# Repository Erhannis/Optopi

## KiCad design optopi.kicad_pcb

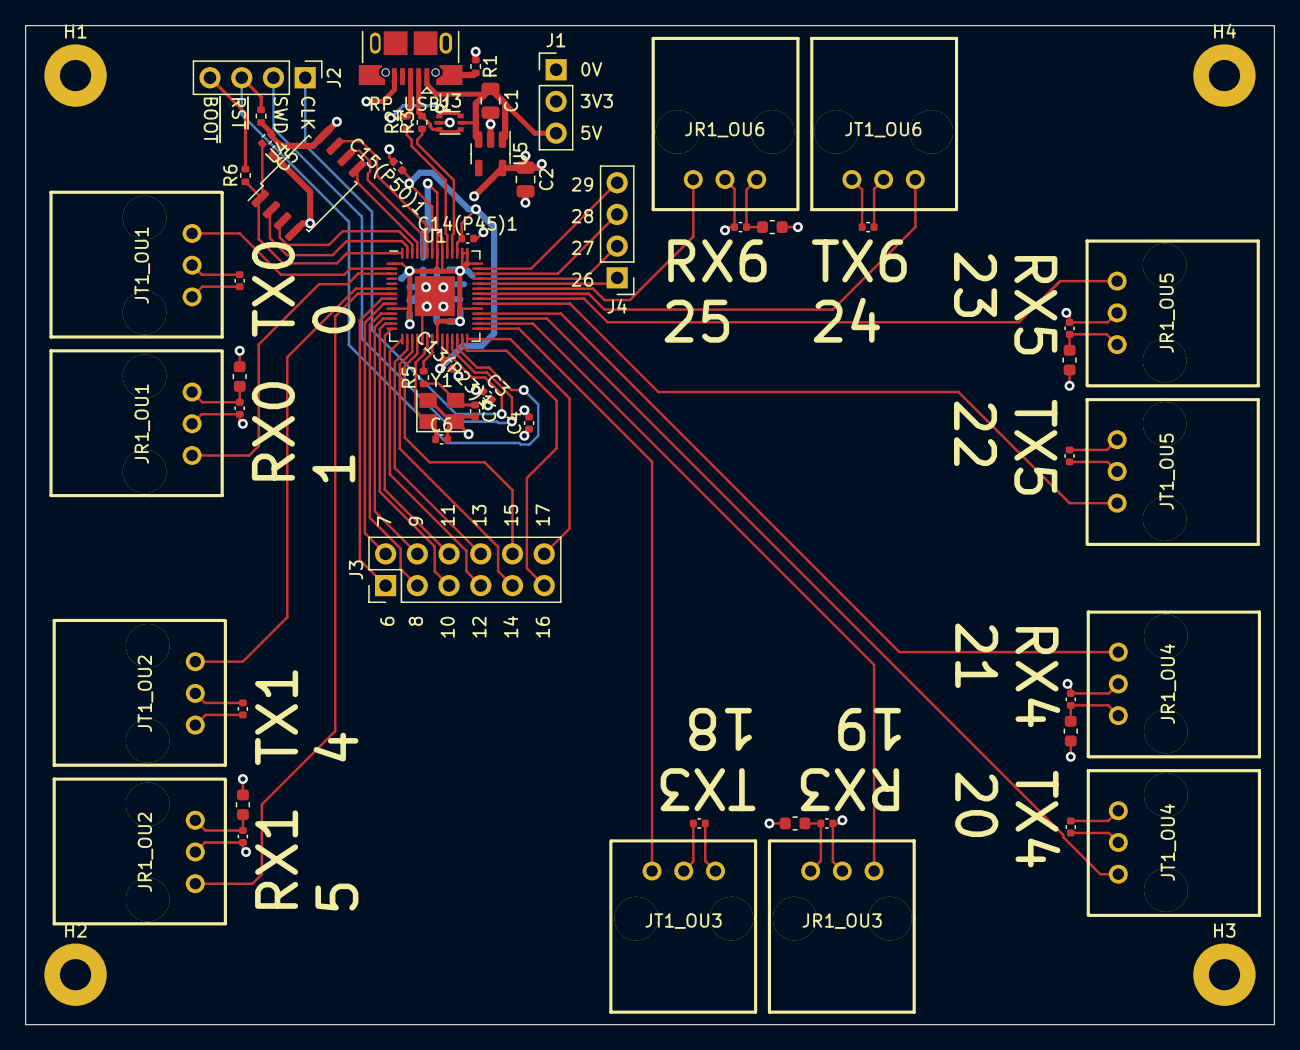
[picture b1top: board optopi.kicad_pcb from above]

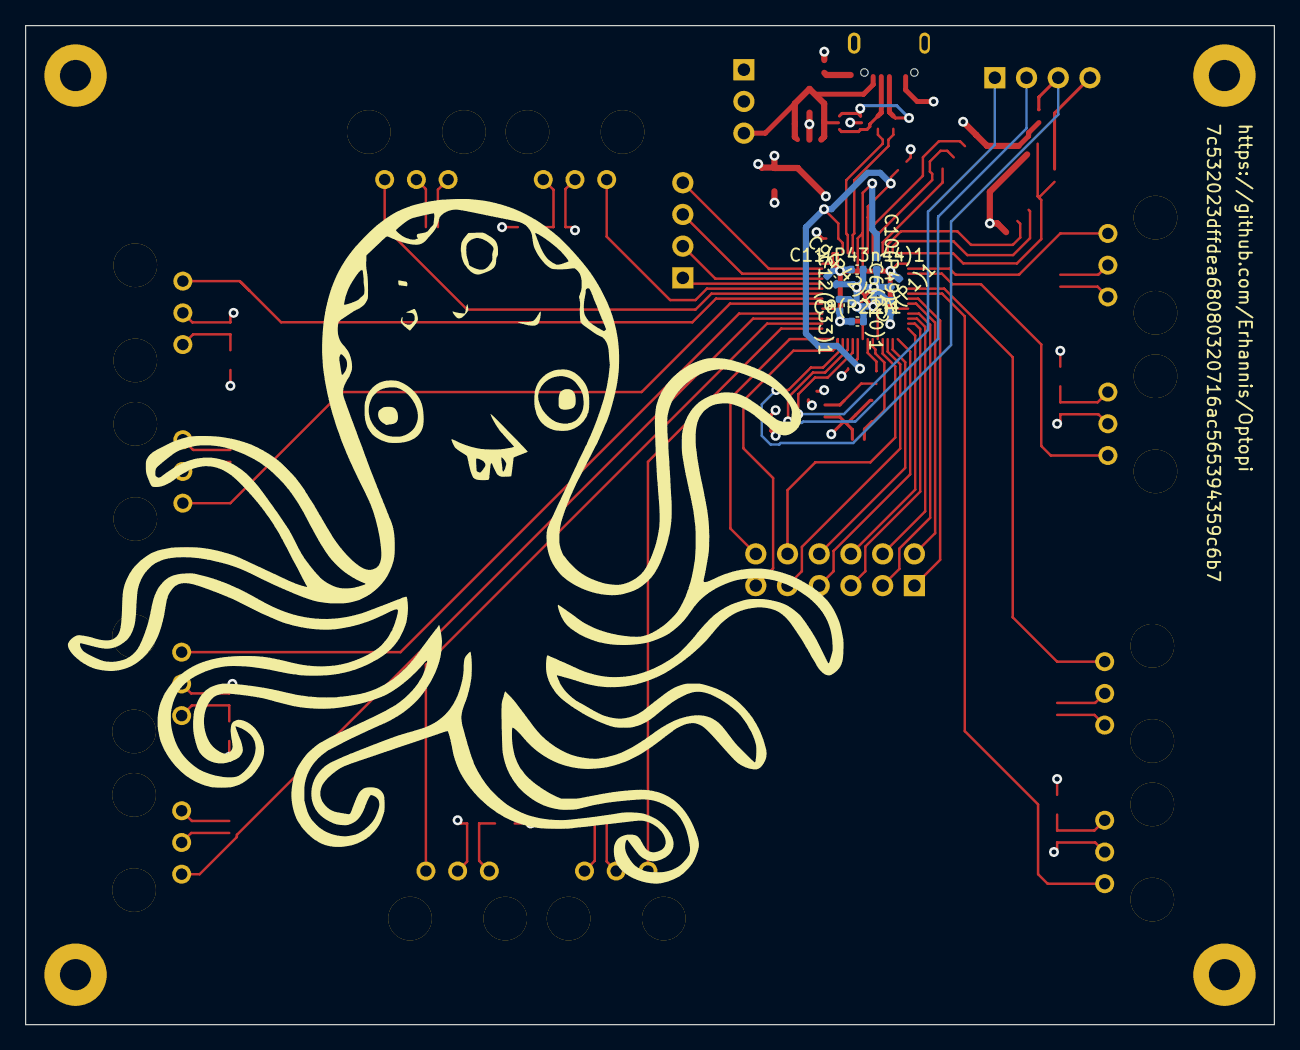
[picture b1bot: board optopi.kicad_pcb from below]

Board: 4 copper layers, 100.0 x 80.0 mm, 68 parts (7 on the bottom side), 56 nets.

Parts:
C1, C2: 10uF; C_0805_2012Metric
C1_OU1, C1_OU2, C1_OU3, C1_OU4, C1_OU5, C1_OU6, C2_OU1, C2_OU2, C2_OU3, C2_OU4, C2_OU5, C2_OU6, C3, C4, C5, C6(P10)1, C7(P1)1, C8(P22)1, C9(P42)1, C10(P49)1, C12(P33)1, C13(P23)1, C15(P50)1: 100nF; C_0402_1005Metric
C6, C7: 35pF; C_0402_1005Metric
C11(P43n44)1, C14(P45)1: 1uF; C_0402_1005Metric
H1, H2, H3, H4: MountingHole_Pad; MountingHole_2.5mm_Pad
J1: Conn_01x03_Pin; PinHeader_1x03_P2.54mm_Vertical
J2, J4: Conn_01x04_Pin; PinHeader_1x04_P2.54mm_Vertical
J3: Conn_02x06_Odd_Even; PinHeader_2x06_P2.54mm_Vertical
JR1_OU1, JR1_OU2, JR1_OU3, JR1_OU4, JR1_OU5, JR1_OU6: ZGY135/T9(PLR); OPTO-TH_ZGY135-T9-PLR
JT1_OU1, JT1_OU2, JT1_OU3, JT1_OU4, JT1_OU5, JT1_OU6: ZGY133/T9(PLT); OPTO-TH_ZGY135-T9-PLR
L1_OU1, L1_OU2, L1_OU3, L1_OU4, L1_OU5, L1_OU6: 47uH; L_0603_1608Metric
R1: 1M; R_0402_1005Metric
R2, R3: 27; R_0402_1005Metric
R4, R7: 10K; R_0402_1005Metric
R5: 1K; R_0402_1005Metric
R6: 1k; R_0402_1005Metric
RP_USB1: USB_B_Micro; USB_Micro-B_XKB_U254-051T-4BH83-F1S
U1: RP2040; QFN-56-1EP_7x7mm_P0.4mm_EP3.2x3.2mm
U3: USBLC6-2P6; SOT-666
U4: W25Q128JVS; SOIC-8_5.23x5.23mm_P1.27mm
U5: AP2112K-3.3; SOT-23-5
Y1: 12MHz; Crystal_SMD_3225-4Pin_3.2x2.5mm

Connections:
+1V2: C13(P23)1.1, C14(P45)1.1, C15(P50)1.1, U1.23 (DVDD), U1.45 (VREG_VOUT), U1.50 (DVDD)
+3V3: C2.1, C2_OU1.2, C2_OU2.2, C2_OU3.2, C2_OU4.2, C2_OU5.2, C2_OU6.2, C3.1, C4.1, C5.1, C6(P10)1.1, C7(P1)1.1, C8(P22)1.1, C9(P42)1.1, C10(P49)1.1, C11(P43n44)1.1, C12(P33)1.1, J1.2, JT1_OU1.2 (VCC), JT1_OU2.2 (VCC), JT1_OU3.2 (VCC), JT1_OU4.2 (VCC), JT1_OU5.2 (VCC), JT1_OU6.2 (VCC), L1_OU1.1, L1_OU2.1, L1_OU3.1, L1_OU4.1, L1_OU5.1, L1_OU6.1, R4.1, R7.2, U1.1 (IOVDD), U1.10 (IOVDD), U1.22 (IOVDD), U1.33 (IOVDD), U1.42 (IOVDD), U1.43 (ADC_AVDD), U1.44 (VREG_IN), U1.48 (USB_VDD), U1.49 (IOVDD), U4.8 (VCC), U5.5 (VOUT)
+5V: C1.1, J1.3, RP_USB1.1 (VBUS), U3.5 (VBUS), U5.1 (VIN), U5.3 (EN)
/QSPI_CS: R6.1, R7.1, U1.56 (QSPI_SS), U4.1 (~CS)
/QSPI_DATA[0]: U1.53 (QSPI_SD0), U4.5 (DI(IO0))
/QSPI_DATA[1]: U1.55 (QSPI_SD1), U4.2 (DO(IO1))
/QSPI_DATA[2]: U1.54 (QSPI_SD2), U4.3 (IO2)
/QSPI_DATA[3]: U1.51 (QSPI_SD3), U4.7 (IO3)
/QSPI_SCK: U1.52 (QSPI_SCLK), U4.6 (CLK)
/RP_SWCLK: J2.1, U1.24 (SWCLK)
/RP_SWD: J2.2, U1.25 (SWD)
/RP_UD+: R2.1, U1.47 (USB_DP)
/RP_UD-: R3.1, U1.46 (USB_DM)
/USB_BOOT: J2.4, R6.2
/optic_uart1/RX: JR1_OU1.1 (VOUT), U1.3 (GPIO1)
/optic_uart1/TX: JT1_OU1.3 (VIN), U1.2 (GPIO0)
/optic_uart2/RX: JR1_OU2.1 (VOUT), U1.7 (GPIO5)
/optic_uart2/TX: JT1_OU2.3 (VIN), U1.6 (GPIO4)
/optic_uart3/RX: JR1_OU3.1 (VOUT), U1.30 (GPIO19)
/optic_uart3/TX: JT1_OU3.3 (VIN), U1.29 (GPIO18)
/optic_uart4/RX: JR1_OU4.1 (VOUT), U1.32 (GPIO21)
/optic_uart4/TX: JT1_OU4.3 (VIN), U1.31 (GPIO20)
/optic_uart5/RX: JR1_OU5.1 (VOUT), U1.35 (GPIO23)
/optic_uart5/TX: JT1_OU5.3 (VIN), U1.34 (GPIO22)
/optic_uart6/RX: JR1_OU6.1 (VOUT), U1.37 (GPIO25)
/optic_uart6/TX: JT1_OU6.3 (VIN), U1.36 (GPIO24)
/~RESET: J2.3, R4.2, U1.26 (RUN)
GND: C1.2, C1_OU1.2, C1_OU2.2, C1_OU3.2, C1_OU4.2, C1_OU5.2, C1_OU6.2, C2.2, C2_OU1.1, C2_OU2.1, C2_OU3.1, C2_OU4.1, C2_OU5.1, C2_OU6.1, C3.2, C4.2, C5.2, C6.2, C6(P10)1.2, C7.2, C7(P1)1.2, C8(P22)1.2, C9(P42)1.2, C10(P49)1.2, C11(P43n44)1.2, C12(P33)1.2, C13(P23)1.2, C14(P45)1.2, C15(P50)1.2, H1.1, H2.1, H3.1, H4.1, J1.1, JR1_OU1.2 (GND), JR1_OU2.2 (GND), JR1_OU3.2 (GND), JR1_OU4.2 (GND), JR1_OU5.2 (GND), JR1_OU6.2 (GND), JT1_OU1.1 (GND), JT1_OU2.1 (GND), JT1_OU3.1 (GND), JT1_OU4.1 (GND), JT1_OU5.1 (GND), JT1_OU6.1 (GND), R1.1, RP_USB1.5 (GND), U1.19 (TESTEN), U1.57 (GND), U3.2 (GND), U4.4 (GND), U5.2 (GND), Y1.2, Y1.4
unnamed: C7.1, R5.1, Y1.3
unnamed: J3.1, U1.8 (GPIO6)
unnamed: J3.2, U1.9 (GPIO7)
unnamed: J3.3, U1.11 (GPIO8)
unnamed: J3.4, U1.12 (GPIO9)
unnamed: J3.5, U1.13 (GPIO10)
unnamed: J3.6, U1.14 (GPIO11)
unnamed: J3.7, U1.15 (GPIO12)
unnamed: J3.8, U1.16 (GPIO13)
unnamed: J3.9, U1.17 (GPIO14)
unnamed: J3.10, U1.18 (GPIO15)
unnamed: J3.11, U1.27 (GPIO16)
unnamed: J3.12, U1.28 (GPIO17)
unnamed: J4.1, U1.38 (GPIO26_ADC0)
unnamed: J4.2, U1.39 (GPIO27_ADC1)
unnamed: J4.3, U1.40 (GPIO28_ADC2)
unnamed: J4.4, U1.41 (GPIO29_ADC3)
unnamed: C1_OU1.1, JR1_OU1.3 (VCC), L1_OU1.2
unnamed: C1_OU2.1, JR1_OU2.3 (VCC), L1_OU2.2
unnamed: C1_OU3.1, JR1_OU3.3 (VCC), L1_OU3.2
unnamed: C1_OU4.1, JR1_OU4.3 (VCC), L1_OU4.2
unnamed: C1_OU5.1, JR1_OU5.3 (VCC), L1_OU5.2
unnamed: C1_OU6.1, JR1_OU6.3 (VCC), L1_OU6.2
unnamed: R2.2, RP_USB1.3 (D+), U3.1 (I/O1), U3.6 (I/O1)
unnamed: R3.2, RP_USB1.2 (D-), U3.3 (I/O2), U3.4 (I/O2)
unnamed: R1.2, RP_USB1.6 (Shield)
unnamed: C6.1, U1.20 (XIN), Y1.1
unnamed: R5.2, U1.21 (XOUT)

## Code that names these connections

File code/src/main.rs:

#![no_std]
#![no_main]

mod pio_run;
mod opto_uart;

use embedded_hal::digital::OutputPin;
use opto_uart::toggle_uart_tx_pin;
use pio_run::uart_tx_putc;
use rp_pico::{entry, pac::clocks};
use defmt::*;
use defmt_rtt as _;
use panic_probe as _;
use core::{fmt::Write, str};

use rp2040_hal::{self as bsp, gpio::{DynBankId, DynPinId}};

use bsp::{
    clocks::{init_clocks_and_plls, Clock},
    pac,
    sio::Sio,
    watchdog::Watchdog,
};

use rp2040_hal::{gpio::Pins, uart::{DataBits, StopBits, UartConfig, UartPeripheral}};
use rp2040_hal::fugit::RateExtU32;

const XOSC_CRYSTAL_FREQ: u32 = 12_000_000; // Typically found in BSP crates

#[entry]
fn main() -> ! {
    info!("Program start");
    let mut peripherals = pac::Peripherals::take().unwrap();
    let sio = Sio::new(peripherals.SIO);
    let pins = Pins::new(peripherals.IO_BANK0, peripherals.PADS_BANK0, sio.gpio_bank0, &mut peripherals.RESETS);

    let mut watchdog = Watchdog::new(peripherals.WATCHDOG);
    let mut clocks = init_clocks_and_plls(XOSC_CRYSTAL_FREQ, peripherals.XOSC, peripherals.CLOCKS, peripherals.PLL_SYS, peripherals.PLL_USB, &mut peripherals.RESETS, &mut watchdog).ok().unwrap();
    let core = pac::CorePeripherals::take().unwrap();

    // let baud = 9600;
    // let baud = 115200;
    let baud = 921600;

    let (mut pio0, sm00, _, _, _) = rp2040_hal::pio::PIOExt::split(peripherals.PIO0, &mut peripherals.RESETS);
    let mut gpio18 = pins.gpio18;
    let uart2_tx_pin = gpio18.id();
    gpio18.set_output_override(rp2040_hal::gpio::OutputOverride::Invert);
    let mut uart2_tx = pio_run::uart_tx_program_init(
      &mut pio0,
      sm00,
      gpio18.into_function(),
      baud,
      &clocks
    );

    let (mut pio1, sm10, _, _, _) = rp2040_hal::pio::PIOExt::split(peripherals.PIO1, &mut peripherals.RESETS);
    let mut gpio19 = pins.gpio19;
    // gpio19.set_input_override(rp2040_hal::gpio::InputOverride::Invert);
    let mut uart2_rx = pio_run::uart_rx_program_init(
      &mut pio1,
      sm10,
      gpio19.into_function(),
      baud,
      &clocks
    );

    let mut delay = cortex_m::delay::Delay::new(core.SYST, clocks.system_clock.freq().to_Hz());

    let mut gpio0 = pins.gpio0;
    let uart0_tx_pin = gpio0.id();
    let mut gpio1 = pins.gpio1;
    gpio0.set_output_override(rp2040_hal::gpio::OutputOverride::Invert);
    // gpio1.set_input_override(rp2040_hal::gpio::InputOverride::Invert);
    let uart_pins_0 = (
        gpio0.into_function(),
        gpio1.into_function(),
    );
    let mut uart0 = UartPeripheral::new(peripherals.UART0, uart_pins_0, &mut peripherals.RESETS)
        .enable(
            UartConfig::new(baud.Hz(), DataBits::Eight, None, StopBits::One),
            clocks.peripheral_clock.freq(),
        ).unwrap();

    let mut gpio4 = pins.gpio4;
    let uart1_tx_pin = gpio4.id();
    let mut gpio5 = pins.gpio5;
    gpio4.set_output_override(rp2040_hal::gpio::OutputOverride::Invert);
    gpio5.set_input_override(rp2040_hal::gpio::InputOverride::Invert);
    let uart_pins_1 = (
        gpio4.into_function(),
        gpio5.into_function(),
    );
    let mut uart1 = UartPeripheral::new(peripherals.UART1, uart_pins_1, &mut peripherals.RESETS)
        .enable(
            UartConfig::new(baud.Hz(), DataBits::Eight, None, StopBits::One),
            clocks.peripheral_clock.freq(),
        ).unwrap();
        
    let mut i = 0;
    loop {
        info!("Loop");

        toggle_uart_tx_pin(&uart0_tx_pin, &mut delay);
        core::write!(uart0, "Hello World 0 {}!\r\n", i).unwrap();
        toggle_uart_tx_pin(&uart1_tx_pin, &mut delay);
        core::write!(uart1, "Hello World 1 {}!\r\n", i).unwrap();
        toggle_uart_tx_pin(&uart2_tx_pin, &mut delay);
        uart_tx_putc(&mut uart2_tx, b'x');
        // uart0.write_full_blocking(b"Hello World 0!\r\n");

        delay.delay_ms(100);

        let mut buf: [u8;256] = [0;256];
        while uart0.uart_is_readable() {
            match uart0.read_raw(&mut buf) {
                Ok(count) => {
                    let b = &mut buf[0..count];
                    convert_to_lossy_utf8(b);
                    info!("Read 0: {:?}", str::from_utf8(b).unwrap());
                },
                Err(e) => {
                    info!("Read 0 error");
                },
            }
        }
        while uart1.uart_is_readable() {
            match uart1.read_raw(&mut buf) {
                Ok(count) => {
                    let b = &mut buf[0..count];
                    convert_to_lossy_utf8(b);
                    info!("Read 1: {:?}", str::from_utf8(b).unwrap());
                },
                Err(e) => {
                    info!("Read 1 error");
                },
            }
        }
        loop {
          //DUMMY Inefficient
          match uart2_rx.read() {
            Some(c) => {info!("Read 2: {:?}", (c >> 24) as u8 as char)},
            None => {break;}
          }
        }
        i += 1;
    }
}

//RAINY Export into separate crate

fn convert_to_lossy_utf8(input: &mut [u8]) {
    for byte in input {
        if !byte.is_ascii() {
            *byte = b'?';
        }
    }
}

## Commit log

2024-07-02 One fiber connection added, I think
2024-07-02 Ok, I think it's about ready to go
2024-07-02 I am silly. I got my pun spelled wrong; fixed now, and it even works better
2024-07-02 Added image and url
2024-07-02 Hash
2024-07-02 Generate gerbers
2024-07-10 Moved things around a bit. Started code.
2024-07-11 Ok, maybe that fixed the git submodule accident. Also, I have data flowing over a TOSLINK cable! That wasn't in the list of cables I thought these might take, but....
2024-07-11 Discovered defective components in my boards. Bleh. Otherwise got a board working.
2024-07-11 BROKEN Working on pio
2024-07-14 Messing with stuff, testing
2024-07-14 Cleanup
2024-07-14 More cleanup
2024-07-14 I SORTOF have a PIO uart tx/rx working! A bit buggy still
2024-08-04 Looks like I was messing with the uart stuff
2024-08-04 Ok, SO found a fix for toggling the pin - but it has a chink in it; I lose probably a few dozen microseconds of rx.
2024-08-04 Aha! I got it to work, just toggling the pin without resetting the uart!
2024-08-04 Refactored, I am pleased
2024-08-04 Refactoring
2024-08-04 Toggle all the pins!
